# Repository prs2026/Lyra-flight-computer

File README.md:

# Lyra-flight-computer
 repo for the lyra flight computer

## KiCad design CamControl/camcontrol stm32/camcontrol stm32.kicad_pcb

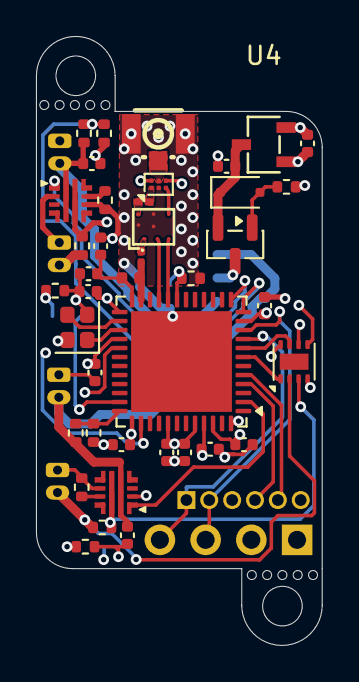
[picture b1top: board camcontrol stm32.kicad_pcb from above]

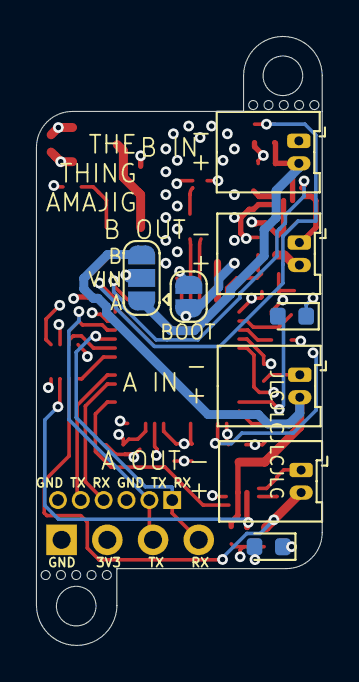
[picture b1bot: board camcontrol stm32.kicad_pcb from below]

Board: 4 copper layers, 15.9 x 33.8 mm, 52 parts (12 on the bottom side), 40 nets.

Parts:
AE1: Antenna_Shield; ANT-SMD_1909763-1
C1, C5, C6, C12: 1u; C_0402_1005Metric
C2: 68p; C_0201_0603Metric
C3: 100p; C_0201_0603Metric
C4, C7: 47n; C_0402_1005Metric
C8, C9, C10, C11, C13, C14, C22: 100n; C_0402_1005Metric
C18: 470n; C_0402_1005Metric
D1, D2: LED; LED_0603_1608Metric
D3: D_Zener; D_SOD-323F
H1, H2: MountingHole; MountingHole_2.2mm_M2_DIN965
J1, J3, J4, J7: Power 1; Molex_PicoBlade_53048-0210_1x02_P1.25mm_Horizontal
J2: Conn_01x04; PinHeader_1x04_P2.54mm_Vertical
J5: Conn_01x06; PinHeader_1x06_P1.27mm_Vertical
J6: Conn_01x02; SolderJumper-2_P1.3mm_Open_RoundedPad1.0x1.5mm
JP1: Jumper; SolderJumper-3_P1.3mm_Open_RoundedPad1.0x1.5mm
L1: 47n; L_0402_1005Metric
Q1: AO3401A; SOT-23
R1, R7: 1k; R_0402_1005Metric
R2, R6: 510; R_0402_1005Metric
R3, R5: 10m; R_0402_1005Metric
R4: 33k; R_0402_1005Metric
R8, R23: 15k; R_0402_1005Metric
R9, R10, R24: 51k; R_0402_1005Metric
U1: BGS12P2L6; Infineon_PG-TSNP-6-10_0.7x1.1mm_0.7x1.1mm_P0.4mm
U2: BALFHB-WL-02D3; CSPG-8_L2.1-W1.8_BALFHB-WL-03D3
U3: STM32WLE4CCUx; QFN-48-1EP_7x7mm_P0.5mm_EP5.6x5.6mm
U4: DS8242; SOT-23-3_L2.9-W1.6-P1.90-LS2.8-BR
U5, U6: TPS25970LRPWR; QFN-10-2x2-hotrod
U7: INA2180; WSON-8-1EP_2x2mm_P0.5mm_EP0.9x1.6mm
Y1: 32MHz; Crystal_SMD_2016-4Pin_2.0x1.6mm

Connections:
+3V3: C6.1, C8.1, C9.1, C10.1, C11.1, C13.1, C14.1, C22.1, D1.2 (A), J2.2, U1.4 (VDD), U3.11 (VDD), U3.25 (VDDPA), U3.28 (VDDRF), U3.37 (VBAT), U3.41 (VDDA), U3.44 (VDD), U3.46 (VDDSMPS), U4.2 (Vout), U7.8 (VS)
+12V: C12.1, J1.2, JP1.1 (A), R23.1, U6.5 (IN)
+12VA: C1.1, J4.2, JP1.3 (B), R8.1, U5.5 (IN)
/BATT SENSE A: R8.2, R9.1, U3.36 (PA13)
/BATT SENSE B: R23.2, R24.1, U3.12 (PA4)
/BOOTSEL: J6.2, R4.2, U3.19 (PH3)
/CAM1 RX: J2.4, J5.1, U3.9 (PA2)
/CAM1 TX: J2.3, J5.2, U3.10 (PA3)
/CAM2 RX: J5.4, U3.4 (PB6)
/CAM2 TX: J5.5, U3.5 (PB7)
/CURRENT SENSE A: U3.7 (PA0), U7.1 (OUT1)
/CURRENT SENSE B: U3.8 (PA1), U7.7 (OUT2)
/LED INDICATION: D2.2 (A), U3.35 (PA12)
/OSC_IN: U3.26 (OSC_IN), Y1.3
/OSC_OUT: U3.27 (OSC_OUT), Y1.1
/PRWA EN: U3.2 (PB4), U5.1 (EN/UVLO)
/PWR A: J7.2, R5.2, U7.2 (IN-1)
/PWR A SENS: R5.1, U5.6 (OUT), U7.3 (IN+1)
/PWR B: J3.2, R3.2, U7.6 (IN-2)
/PWR B SENS: R3.1, U6.6 (OUT), U7.5 (IN+2)
/PWRB EN: U3.13 (PA5), U6.1 (EN/UVLO)
/RF CTRL: U1.6 (CTRL), U3.38 (PC13)
/VFBSMPS: C18.1, U3.29 (VDDRF1V55), U3.45 (VFBSMPS)
/VR_PA: C4.2, C7.2, L1.1, U3.24 (VR_PA)
GND: AE1.2 (Shield), C1.2, C4.1, C5.2, C6.2, C7.1, C8.2, C9.2, C10.2, C11.2, C12.2, C13.2, C14.2, C18.2, C22.2, J1.1, J2.1, J3.1, J4.1, J5.3, J5.6, J6.1, J7.1, R1.2, R2.2, R4.1, R6.2, R7.2, R9.2, R10.2, R24.2, U1.2 (GND), U2.B1 (GND2), U2.B2 (GND3), U2.C2 (GND1), U3.48 (VSSSMPS), U3.49 (VSS), U4.1 (GND), U5.2 (OLVO), U5.8 (GND), U6.2 (OLVO), U6.8 (GND), U7.4 (GND), Y1.2, Y1.4
unnamed: AE1.1 (A), U1.5 (RFIN)
unnamed: D1.1 (K), R1.1
unnamed: D2.1 (K), R7.1
unnamed: D3.2 (A), Q1.1 (G), R10.1
unnamed: C5.1, D3.1 (K), Q1.2 (S), U4.3 (Vin)
unnamed: JP1.2 (C), Q1.3 (D)
unnamed: U1.3 (RF1), U2.C3 (RFI_in)
unnamed: C2.1, U1.1 (RF2)
unnamed: U2.A2 (RFI_N_out), U3.21 (RFI_N)
unnamed: U2.A3 (RFI_P_out), U3.20 (RFI_P)
unnamed: C3.1, U2.A1 (RFO_in)
unnamed: C2.2, U2.C1 (RFO_out)
unnamed: C3.2, L1.2, U3.23 (RFO_HP)
unnamed: R6.1, U5.9 (ILM)
unnamed: R2.1, U6.9 (ILM)

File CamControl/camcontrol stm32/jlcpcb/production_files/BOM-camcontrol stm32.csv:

Comment,Designator,Footprint,LCSC,Quantity
100n,"C10,C11,C13,C14,C22,C8,C9",C_0402_1005Metric,C1525,7
100p,C3,C_0201_0603Metric,C1546,1
10m,"R3,R5",R_0402_1005Metric,C3024467,2
15k,"R23,R8",R_0402_1005Metric,C25756,2
1k,"R1,R7",R_0402_1005Metric,C11702,2
1u,"C1,C12,C5,C6",C_0402_1005Metric,C52923,4
32MHz,Y1,Crystal_SMD_2016-4Pin_2.0x1.6mm,C383840,1
33k,R4,R_0402_1005Metric,C25779,1
470n,C18,C_0402_1005Metric,C47339,1
47n,L1,L_0402_1005Metric,C22334,1
47n,"C4,C7",C_0402_1005Metric,C5142571,2
510,"R2,R6",R_0402_1005Metric,C25123,2
51k,"R10,R24,R9",R_0402_1005Metric,C25794,3
68p,C2,C_0201_0603Metric,C14441,1
AO3401A,Q1,SOT-23,C15127,1
Antenna_Shield,AE1,ANT-SMD_1909763-1,C392444,1
BALFHB-WL-02D3,U2,CSPG-8_L2.1-W1.8_BALFHB-WL-03D3,C5350082,1
BGS12P2L6,U1,Infineon_PG-TSNP-6-10_0.7x1.1mm_0.7x1.1mm_P0.4mm,C3312945,1
DS8242,U4,SOT-23-3_L2.9-W1.6-P1.90-LS2.8-BR,C5884134,1
D_Zener,D3,D_SOD-323F,C7420320,1
INA2180,U7,WSON-8-1EP_2x2mm_P0.5mm_EP0.9x1.6mm,C83224,1
LED,"D1,D2",LED_0603_1608Metric,C89811,2
STM32WLE4CCUx,U3,QFN-48-1EP_7x7mm_P0.5mm_EP5.6x5.6mm,C2888218,1
TPS25970LRPWR,"U5,U6",QFN-10-2x2-hotrod,C3662801,2

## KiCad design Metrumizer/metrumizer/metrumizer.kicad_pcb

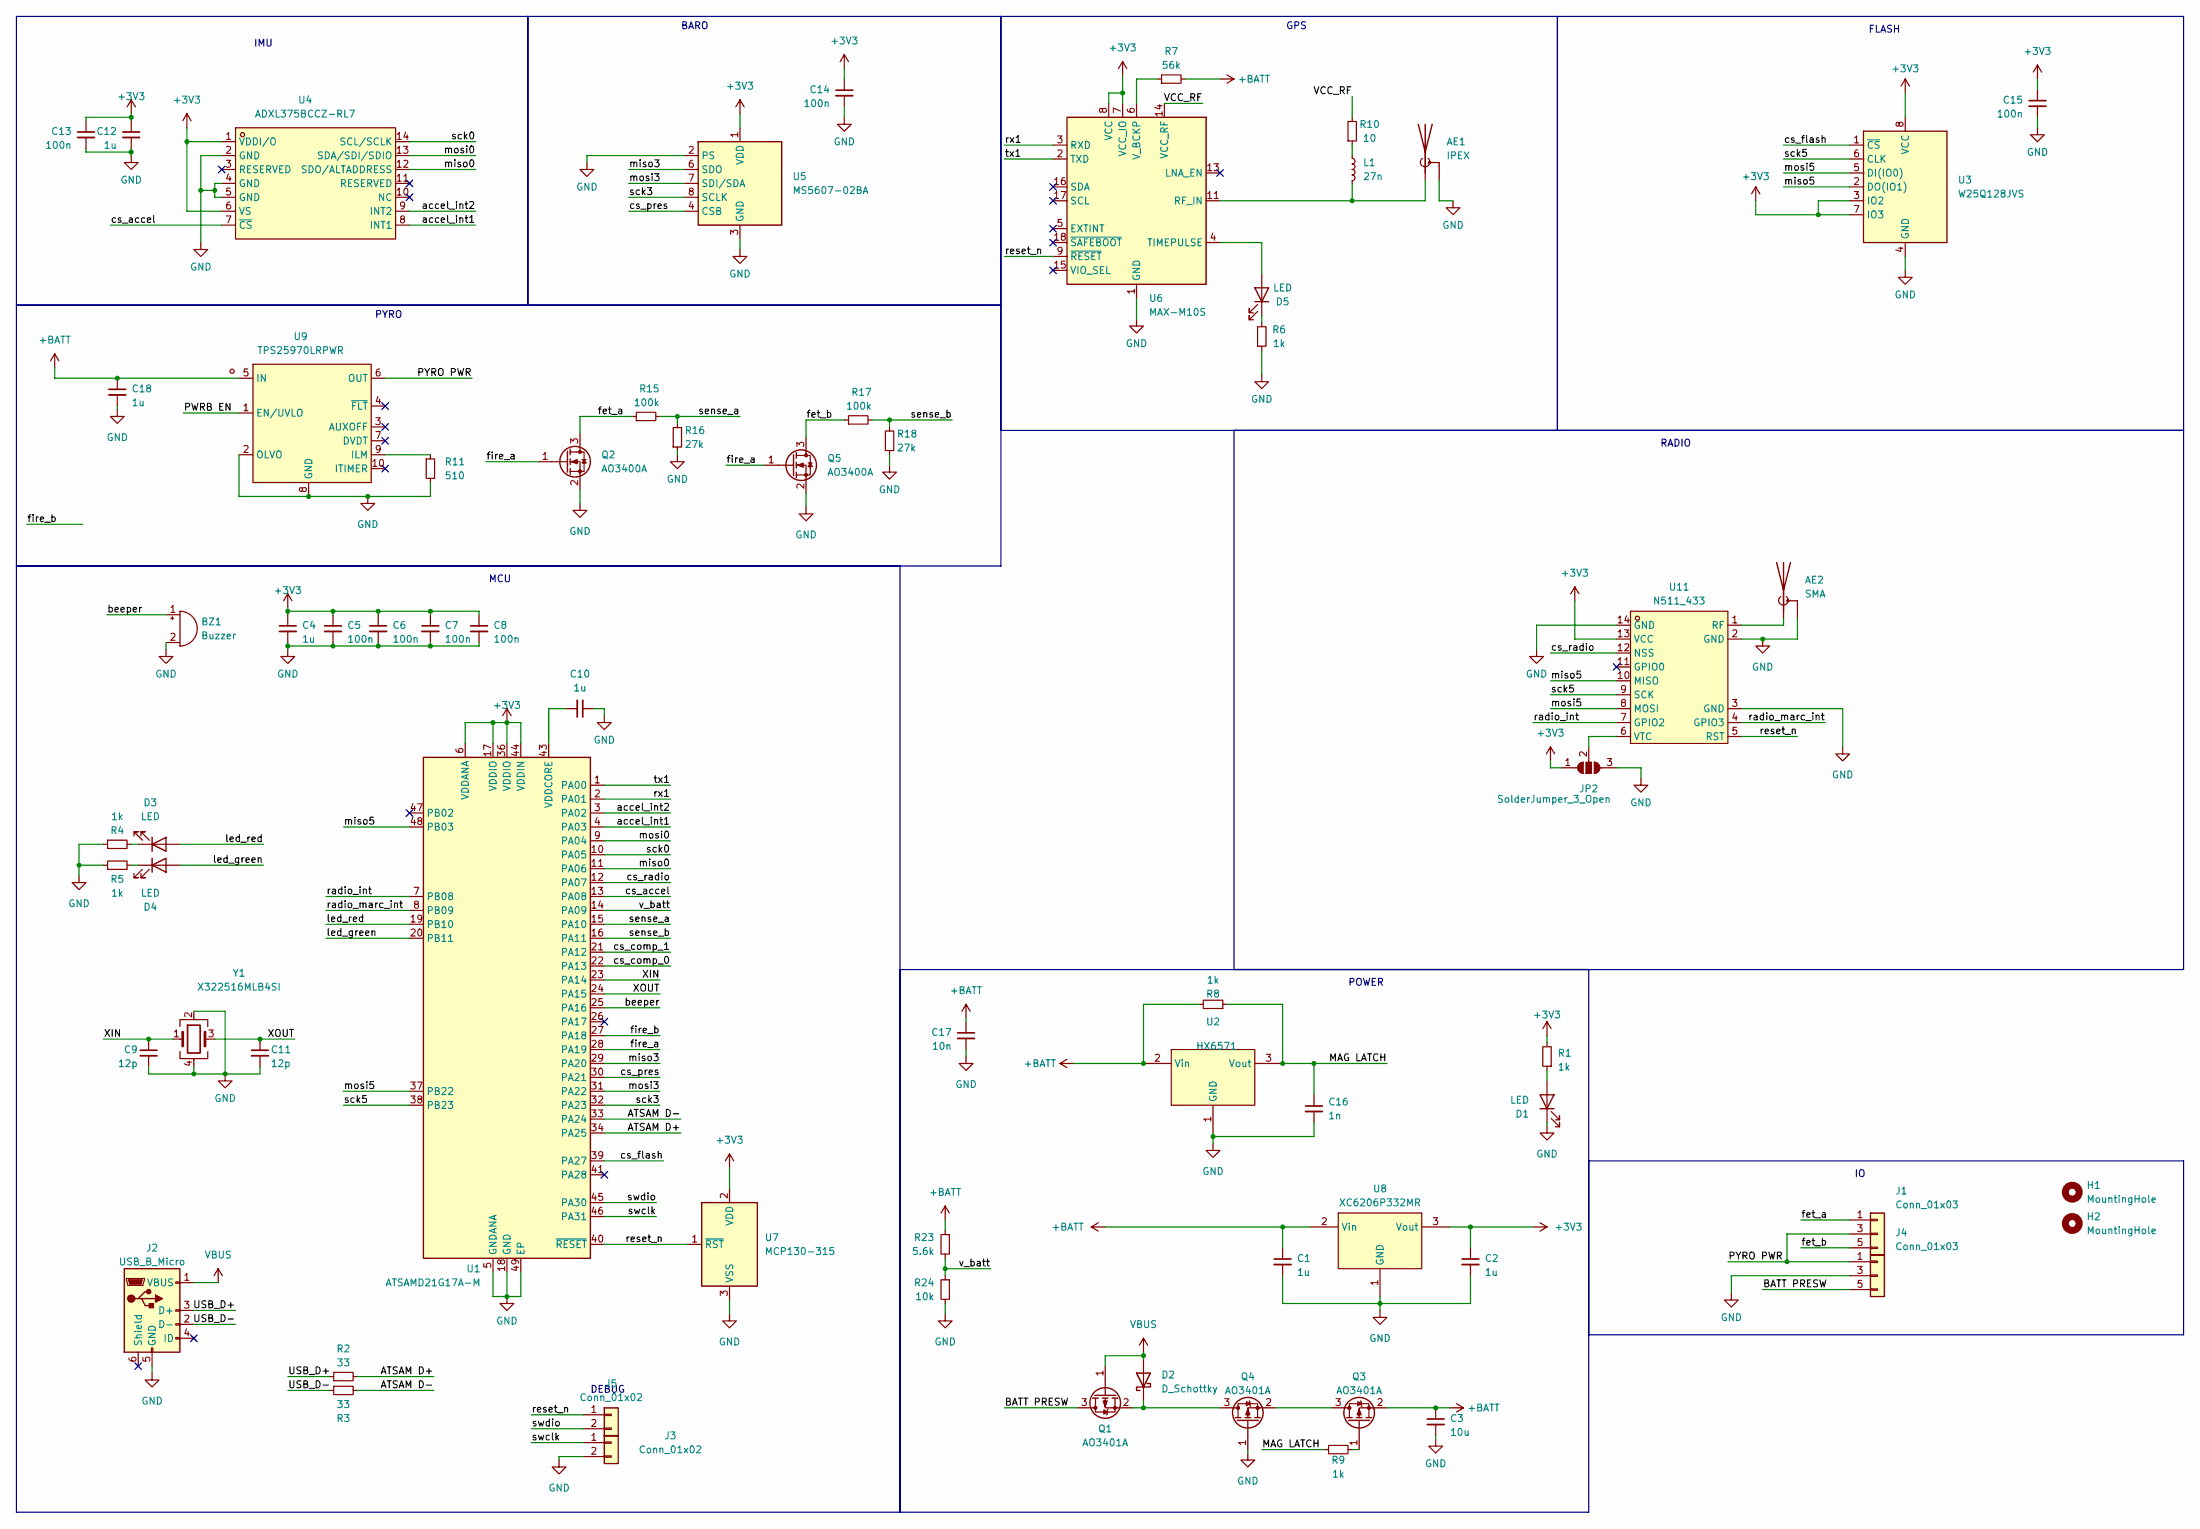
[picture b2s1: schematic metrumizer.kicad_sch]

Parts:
AE1: IPEX; ANT-SMD_1909763-1; LCSC Part C392444
AE2: SMA; CONN-SMD_KH-SMA-KE8-G; LCSC Part C530661
BZ1: Buzzer; PKMCS0909E4000R1; Part # CPE-163
C1, C2, C4, C10, C12, C18: 1u; C_0402_1005Metric; LCSC Part C52923
C3: 10u; C_0603_1608Metric; LCSC Part C96446
C5, C6, C7, C8, C13, C14, C15: 100n; C_0402_1005Metric; LCSC Part C1525
C9, C11: 12p; C_0402_1005Metric; LCSC Part C1547
C16: 1n; C_0402_1005Metric; LCSC Part C1523
C17: 10n; C_0402_1005Metric; LCSC Part C15195
D1, D3, D4, D5: LED; LED_0805_2012Metric
D2: D_Schottky; D_SOD-323F; LCSC Part C191023
H1, H2: MountingHole; MountingHole_3.2mm_M3
J1, J4: Conn_01x03; CONN3_2059-303&slash_998-403_WAG; Part # 2059-323/998-403
J2: USB_B_Micro; MICRO-USB-SMD_U254-051T-4BHJ25-F2S; LCSC Part C381143
J3, J5: Conn_01x02; SolderJumper-2_P1.3mm_Open_Pad1.0x1.5mm
JP2: SolderJumper_3_Open; SolderJumper-3_P1.3mm_Open_RoundedPad1.0x1.5mm
L1: 27n; L_0402_1005Metric; Part # LQG15HS27NJ02D; LCSC Part C18830
Q1, Q3, Q4: AO3401A; SOT-23; LCSC Part C15127
Q2, Q5: AO3400A; SOT-23
R1, R4, R5, R6, R8, R9: 1k; R_0402_1005Metric; LCSC Part C11702
R2, R3: 33; R_0402_1005Metric; LCSC Part C25105
R7: 56k; R_0402_1005Metric; LCSC Part C25796
R10: 10; R_0402_1005Metric; LCSC Part C11702
R11: 510; R_0402_1005Metric; LCSC Part C25123
R15, R17: 100k; R_0402_1005Metric; LCSC Part C11702
R16, R18: 27k; R_0402_1005Metric; LCSC Part C25771
R23: 5.6k; R_0402_1005Metric; LCSC Part C25908
R24: 10k; R_0402_1005Metric; LCSC Part C25744
U1: ATSAMD21G17A-M; QFN-48-1EP_7x7mm_P0.5mm_EP5.15x5.15mm; LCSC Part C614532
U2: HX6571; SOT-23-3_L2.9-W1.6-P1.90-LS2.8-BR; LCSC Part C495738
U3: W25Q128JVS; SOIC-8_5.23x5.23mm_P1.27mm; LCSC Part C97521
U4: ADXL375BCCZ-RL7; LGA-14_L5.0-W3.0-P0.80-BL; LCSC Part C481898
U5: MS5607-02BA; LGA-8_3x5mm_P1.25mm; LCSC Part C97627
U6: MAX-M10S; ublox_MAX
U7: MCP130-315; SOT-23; LCSC Part C625194
U8: XC6206P332MR; SOT-23-3; LCSC Part C5446
U9: TPS25970LRPWR; QFN-10-2x2-hotrod; LCSC Part C3662801
U11: N511_433; N511 433
Y1: X322516MLB4SI; Crystal_SMD_3225-4Pin_3.2x2.5mm; LCSC Part C5444547

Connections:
+3V3: C2.1, C4.1, C5.1, C6.1, C7.1, C8.1, C12.1, C13.1, C14.1, C15.1, JP2.1 (A), R1.2, U1.6 (VDDANA), U1.17 (VDDIO), U1.36 (VDDIO), U1.44 (VDDIN), U3.3 (IO2), U3.7 (IO3), U3.8 (VCC), U4.1 (VDDI/O), U4.6 (VS), U5.1 (VDD), U6.7 (VCC_IO), U6.8 (VCC), U7.2 (VDD), U8.3 (Vout), U11.13 (VCC)
+BATT: C1.1, C3.1, C17.1, C18.1, Q3.2 (S), R7.2, R8.2, R23.1, U2.2 (Vin), U8.2 (Vin), U9.5 (IN)
/ATSAM D+: R2.2, U1.34 (PA25)
/ATSAM D-: R3.2, U1.33 (PA24)
/BATT PRESW: J4.5 (Pin_3), J4.6 (Pin_3), Q1.3 (D)
/MAG LATCH: C16.1, R8.1, R9.1, U2.3 (Vout)
/PWRB EN: U9.1 (EN/UVLO)
/PYRO PWR: J1.3 (Pin_2), J1.4 (Pin_2), J4.1, J4.2 (Pin_1), U9.6 (OUT)
/USB_D+: J2.3 (D+), R2.1
/USB_D-: J2.2 (D-), R3.1
/VCC_RF: R10.2, U6.14 (VCC_RF)
/XIN: C9.1, U1.23 (PA14), Y1.1
/XOUT: C11.1, U1.24 (PA15), Y1.3
/accel_int1: U1.4 (PA03), U4.8 (INT1)
/accel_int2: U1.3 (PA02), U4.9 (INT2)
/beeper: BZ1.1 (+), U1.25 (PA16)
/cs_accel: U1.13 (PA08), U4.7 (~CS)
/cs_comp_0: U1.22 (PA13)
/cs_comp_1: U1.21 (PA12)
/cs_flash: U1.39 (PA27), U3.1 (~CS)
/cs_pres: U1.30 (PA21), U5.4 (CSB), U5.5 (CSB)
/cs_radio: U1.12 (PA07), U11.12 (NSS)
/fet_a: J1.1, J1.2 (Pin_1), Q2.3 (D), R15.1
/fet_b: J1.5 (Pin_3), J1.6 (Pin_3), Q5.3 (D), R17.1
/fire_a: Q2.1 (G), Q5.1 (G), U1.28 (PA19)
/fire_b: U1.27 (PA18)
/led_green: D4.2 (A), U1.20 (PB11)
/led_red: D3.2 (A), U1.19 (PB10)
/miso0: U1.11 (PA06), U4.12 (SDO/ALTADDRESS)
/miso3: U1.29 (PA20), U5.6 (SDO)
/miso5: U1.48 (PB03), U3.2 (DO(IO1)), U11.10 (MISO)
/mosi0: U1.9 (PA04), U4.13 (SDA/SDI/SDIO)
/mosi3: U1.31 (PA22), U5.7 (SDI/SDA)
/mosi5: U1.37 (PB22), U3.5 (DI(IO0)), U11.8 (MOSI)
/radio_int: U1.7 (PB08), U11.7 (GPIO2)
/radio_marc_int: U1.8 (PB09), U11.4 (GPIO3)
/reset_n: J5.1, U1.40 (~RESET), U6.9 (~RESET), U7.1 (~RST), U11.5 (RST)
/rx1: U1.2 (PA01), U6.3 (RXD)
/sck0: U1.10 (PA05), U4.14 (SCL/SCLK)
/sck3: U1.32 (PA23), U5.8 (SCLK)
/sck5: U1.38 (PB23), U3.6 (CLK), U11.9 (SCK)
/sense_a: R15.2, R16.2, U1.15 (PA10)
/sense_b: R17.2, R18.2, U1.16 (PA11)
/swclk: J3.1, U1.46 (PA31)
/swdio: J5.2, U1.45 (PA30)
/tx1: U1.1 (PA00), U6.2 (TXD)
/v_batt: R23.2, R24.1, U1.14 (PA09)
GND: AE1.2 (Shield), AE2.2 (Shield), BZ1.2 (-), C1.2, C2.2, C3.2, C4.2, C5.2, C6.2, C7.2, C8.2, C9.2, C10.1, C11.2, C12.2, C13.2, C14.2, C15.2, C16.2, C17.2, C18.2, D1.1 (K), J2.5 (GND), J3.2, J4.3 (Pin_2), J4.4 (Pin_2), JP2.3 (B), Q2.2 (S), Q4.1 (G), Q5.2 (S), R4.1, R5.1, R6.1, R11.2, R16.1, R18.1, R24.2, U1.5 (GNDANA), U1.18 (GND), U1.35 (GND), U1.42 (GND), U1.49 (EP), U2.1 (GND), U3.4 (GND), U4.2 (GND), U4.4 (GND), U4.5 (GND), U5.2 (PS), U5.3 (GND), U6.1 (GND), U6.10 (GND), U6.12 (GND), U7.3 (VSS), U8.1 (GND), U9.2 (OLVO), U9.8 (GND), U11.2 (GND), U11.3 (GND), U11.14 (GND), Y1.2, Y1.4
unnamed: AE1.1 (A), L1.2, U6.11 (RF_IN)
unnamed: AE2.1 (A), U11.1 (RF)
unnamed: D1.2 (A), R1.1
unnamed: D2.1 (K), Q1.2 (S), Q4.3 (D)
unnamed: D3.1 (K), R4.2
unnamed: D4.1 (K), R5.2
unnamed: D5.2 (A), U6.4 (TIMEPULSE)
unnamed: D5.1 (K), R6.2
unnamed: JP2.2 (C), U11.6 (VTC)
unnamed: L1.1, R10.1
unnamed: Q3.3 (D), Q4.2 (S)
unnamed: Q3.1 (G), R9.2
unnamed: C10.2, U1.43 (VDDCORE)
unnamed: R7.1, U6.6 (V_BCKP)
unnamed: R11.1, U9.9 (ILM)
VBUS: D2.2 (A), J2.1 (VBUS), Q1.1 (G)

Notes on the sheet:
IMU
PYRO
DEBUG
GPS
MCU
BARO
RADIO
POWER
FLASH

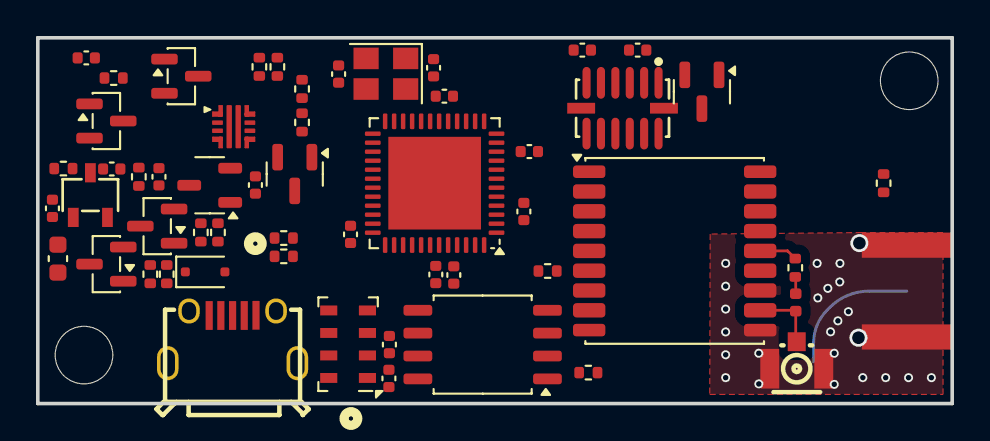
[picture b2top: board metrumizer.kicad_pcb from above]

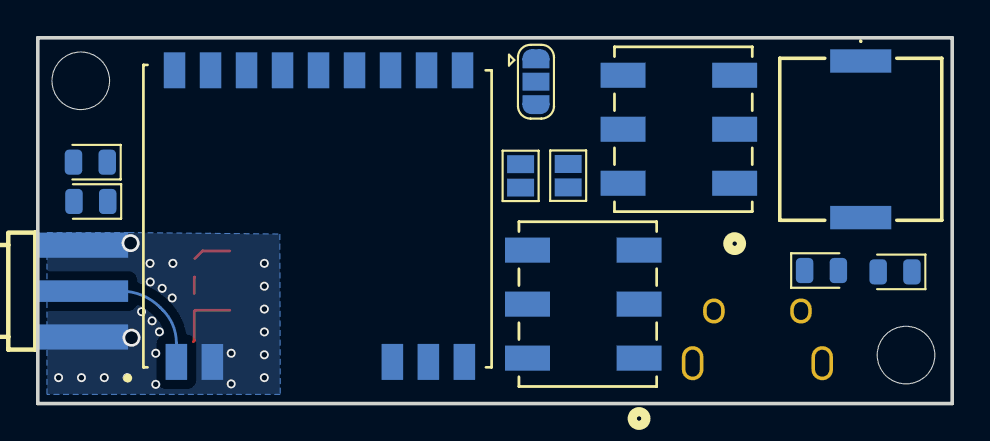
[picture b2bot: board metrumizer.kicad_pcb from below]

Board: 4 copper layers, 50.8 x 20.3 mm, 68 parts (13 on the bottom side), 60 nets.

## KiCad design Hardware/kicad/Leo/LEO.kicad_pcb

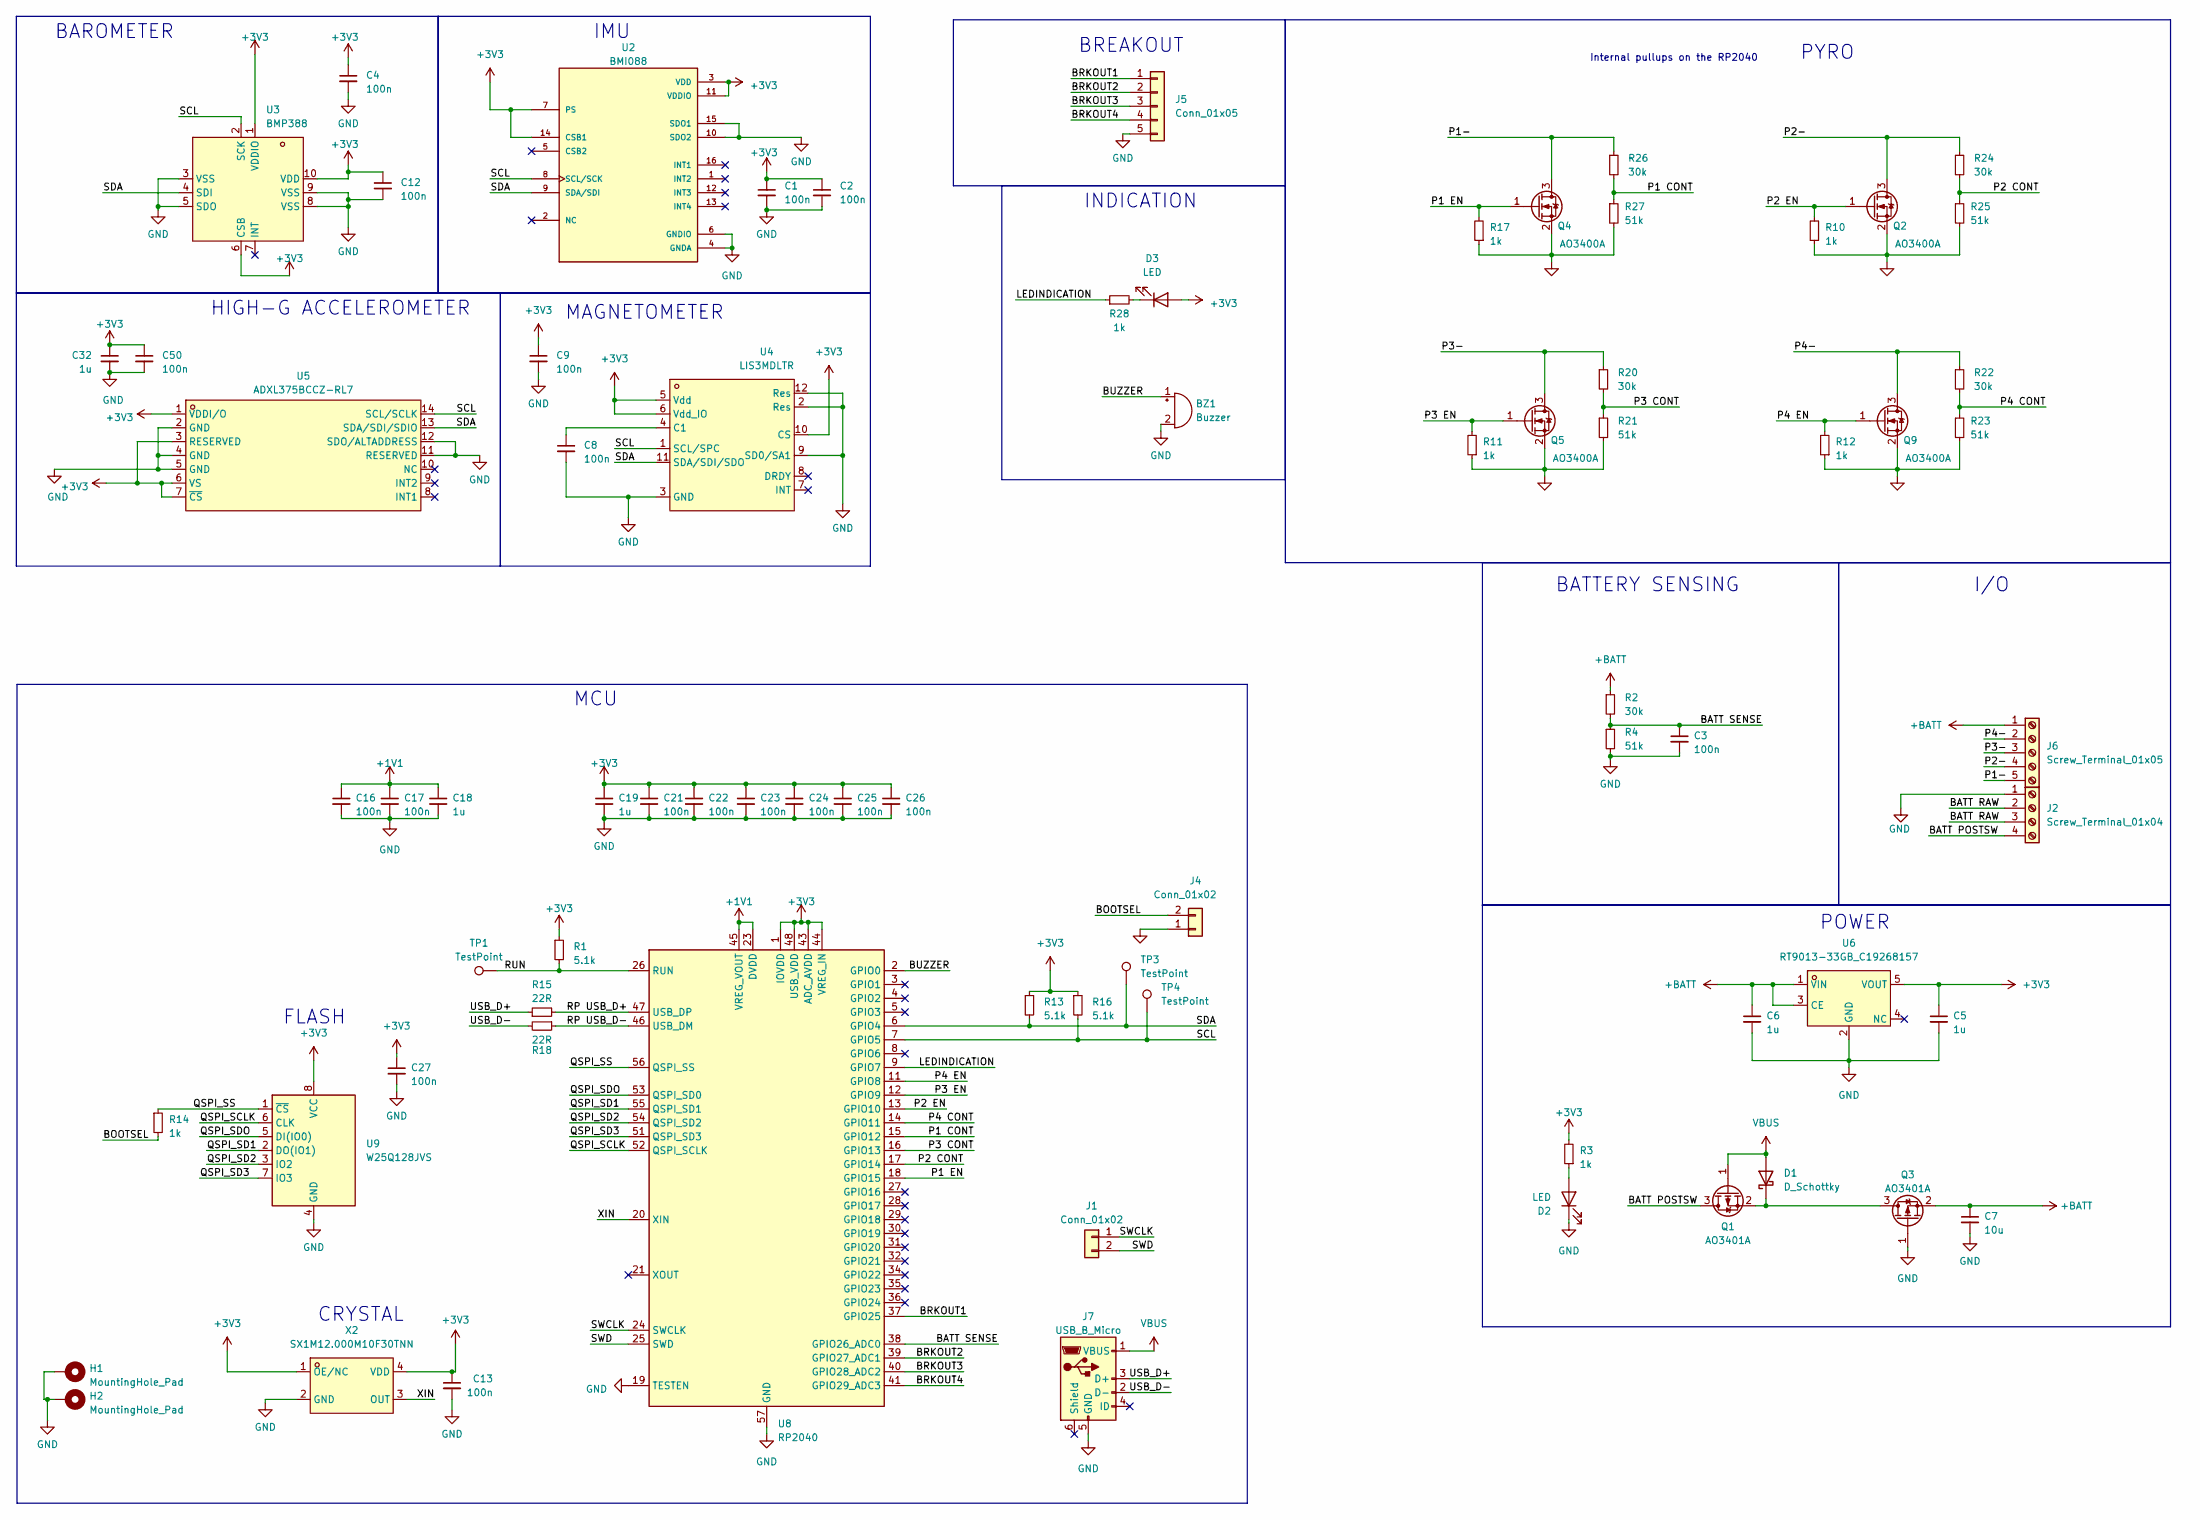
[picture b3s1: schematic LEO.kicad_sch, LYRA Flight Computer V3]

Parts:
BZ1: Buzzer; PKMCS0909E4000R1; Part # CPE-163
C1, C2, C3, C4, C8, C9, C12, C13, C16, C17, C21, C22, C23, C24, C25, C26, C27, C50: 100n; C_0402_1005Metric; LCSC Part C1525
C5, C6, C18, C19, C32: 1u; C_0402_1005Metric; LCSC Part C52923
C7: 10u; C_0603_1608Metric; LCSC Part C96446
D1: D_Schottky; D_SOD-323F; LCSC Part C191023
D2, D3: LED; LED_0805_2012Metric
H1, H2: MountingHole_Pad; MountingHole_2.2mm_M2_DIN965_Pad
J1: Conn_01x02; SolderJumper-2_P1.3mm_Open_Pad1.0x1.5mm
J2: Screw_Terminal_01x04; TerminalBlock_Phoenix_MPT-0,5-4-2.54_1x04_P2.54mm_Horizontal
J4: Conn_01x02; SolderJumper-2_P1.3mm_Open_RoundedPad1.0x1.5mm
J5: Conn_01x05; Pad_01x_05
J6: Screw_Terminal_01x05; TerminalBlock_Phoenix_MPT-0,5-5-2.54_1x05_P2.54mm_Horizontal
J7: USB_B_Micro; MICRO-USB-SMD_U254-051T-4BHJ25-F2S; LCSC Part C381143
Q1, Q3: AO3401A; SOT-23; LCSC Part C15127
Q2, Q4, Q5, Q9: AO3400A; SOT-23; LCSC Part C20917
R1, R13, R16: 5.1k; R_0402_1005Metric; LCSC Part C25905
R2, R20, R22, R24, R26: 30k; R_0402_1005Metric; LCSC Part C25105
R3, R10, R11, R12, R14, R17, R28: 1k; R_0402_1005Metric; LCSC Part C11702
R4, R21, R23, R25, R27: 51k; R_0402_1005Metric
R15, R18: 22R; R_0402_1005Metric; LCSC Part C25092
TP1, TP3, TP4: TestPoint; TestPoint_Pad_1.0x1.0mm
U2: BMI088; LGA-16_L4.5-W3.0-P0.50-BL; LCSC Part C194919
U3: BMP388; SENSORM-SMD_BMP388; LCSC Part C779278
U4: LIS3MDLTR; LGA-12_L2.0-W2.0-P0.50-BL; LCSC Part C478483
U5: ADXL375BCCZ-RL7; LGA-14_L5.0-W3.0-P0.80-BL; LCSC Part C481898
U6: RT9013-33GB_C19268157; SOT-23-5_L2.9-W1.6-P0.95-LS2.8-BR; LCSC Part C19268157
U8: RP2040; QFN-56-1EP_7x7mm_P0.4mm_EP3.2x3.2mm; LCSC Part C2040
U9: W25Q128JVS; SOIC-8_5.23x5.23mm_P1.27mm; LCSC Part C97521
X2: SX1M12.000M10F30TNN; OSC-SMD_4P-L2.0-W1.6-BL; LCSC Part C2901608

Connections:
+1V1: C16.1, C17.1, C18.1, U8.23 (DVDD), U8.45 (VREG_VOUT), U8.50 (DVDD)
+3V3: C1.1, C2.1, C4.1, C5.1, C9.1, C12.1, C13.1, C19.1, C21.1, C22.1, C23.1, C24.1, C25.1, C26.1, C27.1, C32.1, C50.1, D3.2 (A), R1.1, R3.2, R13.1, R16.1, U2.3 (VDD), U2.7 (PS), U2.11 (VDDIO), U2.14 (CSB1), U3.1 (VDDIO), U3.6 (CSB), U3.10 (VDD), U4.5 (Vdd), U4.6 (Vdd_IO), U4.10 (CS), U5.1 (VDDI/O), U5.3 (RESERVED), U5.6 (VS), U5.7 (~CS), U6.5 (VOUT), U8.1 (IOVDD), U8.10 (IOVDD), U8.22 (IOVDD), U8.33 (IOVDD), U8.42 (IOVDD), U8.43 (ADC_AVDD), U8.44 (VREG_IN), U8.48 (USB_VDD), U8.49 (IOVDD), U9.8 (VCC), X2.1 (OE/NC), X2.4 (VDD)
+BATT: C6.1, C7.1, J6.1, Q3.2 (S), R2.1, U6.1 (VIN), U6.3 (CE)
/BATT POSTSW: J2.4, Q1.3 (D)
/BATT RAW: J2.2, J2.3
/BATT SENSE: C3.1, R2.2, R4.1, U8.38 (GPIO26_ADC0)
/BOOTSEL: J4.2, R14.2
/BRKOUT1: J5.1, U8.37 (GPIO25)
/BRKOUT2: J5.2, U8.39 (GPIO27_ADC1)
/BRKOUT3: J5.3, U8.40 (GPIO28_ADC2)
/BRKOUT4: J5.4, U8.41 (GPIO29_ADC3)
/BUZZER: BZ1.1 (+), U8.2 (GPIO0)
/LEDINDICATION: R28.1, U8.9 (GPIO7)
/P1 CONT: R26.2, R27.1, U8.15 (GPIO12)
/P1 EN: Q4.1 (G), R17.2, U8.18 (GPIO15)
/P1-: J6.5, Q4.3 (D), R26.1
/P2 CONT: R24.2, R25.1, U8.17 (GPIO14)
/P2 EN: Q2.1 (G), R10.2, U8.13 (GPIO10)
/P2-: J6.4, Q2.3 (D), R24.1
/P3 CONT: R20.2, R21.1, U8.16 (GPIO13)
/P3 EN: Q5.1 (G), R11.2, U8.12 (GPIO9)
/P3-: J6.3, Q5.3 (D), R20.1
/P4 CONT: R22.2, R23.1, U8.14 (GPIO11)
/P4 EN: Q9.1 (G), R12.2, U8.11 (GPIO8)
/P4-: J6.2, Q9.3 (D), R22.1
/QSPI_SCLK: U8.52 (QSPI_SCLK), U9.6 (CLK)
/QSPI_SD1: U8.55 (QSPI_SD1), U9.2 (DO(IO1))
/QSPI_SD2: U8.54 (QSPI_SD2), U9.3 (IO2)
/QSPI_SD3: U8.51 (QSPI_SD3), U9.7 (IO3)
/QSPI_SDO: U8.53 (QSPI_SD0), U9.5 (DI(IO0))
/QSPI_SS: R14.1, U8.56 (QSPI_SS), U9.1 (~CS)
/RP USB_D+: R15.2, U8.47 (USB_DP)
/RP USB_D-: R18.1, U8.46 (USB_DM)
/RUN: R1.2, TP1.1, U8.26 (RUN)
/SCL: R16.2, TP4.1, U2.8 (SCL/SCK), U3.2 (SCK), U4.1 (SCL/SPC), U5.14 (SCL/SCLK), U8.7 (GPIO5)
/SDA: R13.2, TP3.1, U2.9 (SDA/SDI), U3.4 (SDI), U4.11 (SDA/SDI/SDO), U5.13 (SDA/SDI/SDIO), U8.6 (GPIO4)
/SWCLK: J1.1, U8.24 (SWCLK)
/SWD: J1.2, U8.25 (SWD)
/USB_D+: J7.3 (D+), R15.1
/USB_D-: J7.2 (D-), R18.2
/XIN: U8.20 (XIN), X2.3 (OUT)
GND: BZ1.2 (-), C1.2, C2.2, C3.2, C4.2, C5.2, C6.2, C7.2, C8.2, C9.2, C12.2, C13.2, C16.2, C17.2, C18.2, C19.2, C21.2, C22.2, C23.2, C24.2, C25.2, C26.2, C27.2, C32.2, C50.2, D2.1 (K), H1.1, H2.1, J2.1, J4.1, J5.5, J7.5 (GND), Q2.2 (S), Q3.1 (G), Q4.2 (S), Q5.2 (S), Q9.2 (S), R4.2, R10.1, R11.1, R12.1, R17.1, R21.2, R23.2, R25.2, R27.2, U2.4 (GNDA), U2.6 (GNDIO), U2.10 (SDO2), U2.15 (SDO1), U3.3 (VSS), U3.5 (SDO), U3.8 (VSS), U3.9 (VSS), U4.2 (Res), U4.3 (GND), U4.9 (SD0/SA1), U4.12 (Res), U5.2 (GND), U5.4 (GND), U5.5 (GND), U5.11 (RESERVED), U5.12 (SDO/ALTADDRESS), U6.2 (GND), U8.19 (TESTEN), U8.57 (GND), U9.4 (GND), X2.2 (GND)
unnamed: D1.1 (K), Q1.2 (S), Q3.3 (D)
unnamed: D2.2 (A), R3.1
unnamed: D3.1 (K), R28.2
unnamed: C8.1, U4.4 (C1)
VBUS: D1.2 (A), J7.1 (VBUS), Q1.1 (G)

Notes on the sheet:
HIGH-G ACCELEROMETER
I/O
CRYSTAL
FLASH
IMU
POWER
MAGNETOMETER
BATTERY SENSING
Internal pullups on the RP2040
INDICATION
MCU
PYRO
BAROMETER
BREAKOUT

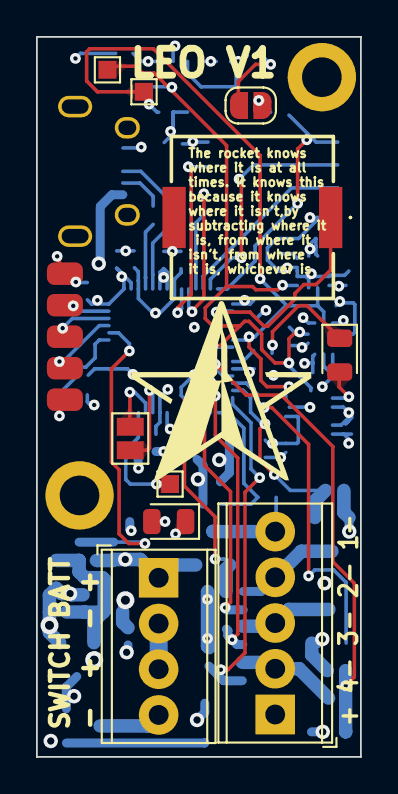
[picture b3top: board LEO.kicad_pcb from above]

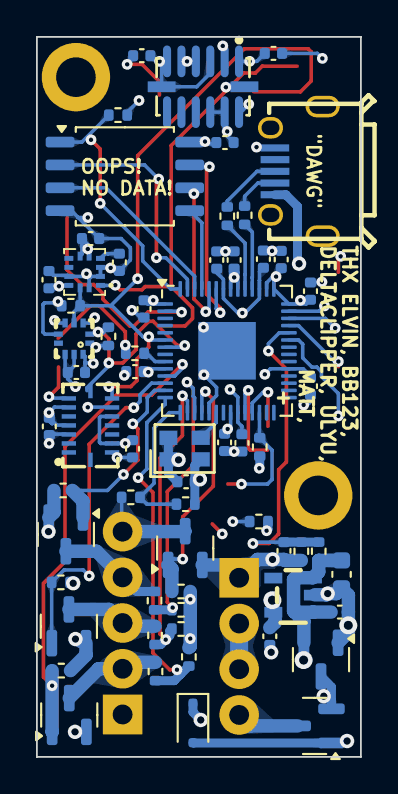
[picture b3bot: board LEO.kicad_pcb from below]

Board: 4 copper layers, 18.0 x 40.0 mm, 75 parts (62 on the bottom side), 47 nets.

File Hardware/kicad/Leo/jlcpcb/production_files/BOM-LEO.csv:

Comment,Designator,Footprint,LCSC
1k,"R10,R11,R12,R14,R17,R28,R3",R_0402_1005Metric,C11702
AO3401A,"Q1,Q3",SOT-23,C15127
100n,"C1,C12,C13,C16,C17,C2,C21,C22,C23,C24,C25,C26,C27,C3,C4,C50,C8,C9",C_0402_1005Metric,C1525
D_Schottky,D1,D_SOD-323F,C191023
RT9013-33GB_C19268157,U6,SOT-23-5_L2.9-W1.6-P0.95-LS2.8-BR,C19268157
BMI088,U2,LGA-16_L4.5-W3.0-P0.50-BL,C194919
RP2040,U8,QFN-56-1EP_7x7mm_P0.4mm_EP3.2x3.2mm,C2040
AO3400A,"Q2,Q4,Q5,Q9",SOT-23,C20917
22R,"R15,R18",R_0402_1005Metric,C25092
30k,"R2,R20,R22,R24,R26",R_0402_1005Metric,C25105
51k,"R21,R23,R25,R27,R4",R_0402_1005Metric,C25794
5.1k,"R1,R13,R16",R_0402_1005Metric,C25905
SX1M12.000M10F30TNN,X2,OSC-SMD_4P-L2.0-W1.6-BL,C2901608
USB_B_Micro,J7,MICRO-USB-SMD_U254-051T-4BHJ25-F2S,C381143
LIS3MDLTR,U4,LGA-12_L2.0-W2.0-P0.50-BL,C478483
ADXL375BCCZ-RL7,U5,LGA-14_L5.0-W3.0-P0.80-BL,C481898
1u,"C18,C19,C32,C5,C6",C_0402_1005Metric,C52923
BMP388,U3,SENSORM-SMD_BMP388,C779278
10u,C7,C_0603_1608Metric,C96446
W25Q128JVS,U9,SOIC-8_5.23x5.23mm_P1.27mm,C97521

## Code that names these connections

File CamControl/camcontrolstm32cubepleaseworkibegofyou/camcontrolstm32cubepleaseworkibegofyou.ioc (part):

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Mcu.Name=STM32WLE5CCUx
Mcu.Package=UFQFPN48
Mcu.UserName=STM32WLE5CCUx
PA12.Signal=GPIO_Output
PA13.GPIOParameters=GPIO_Label
PA13.GPIO_Label=BATT SENSE A
PA13.Mode=IN9
PA13.Signal=ADC_IN9
PA2.Mode=Asynchronous
PA2.Signal=USART2_TX
PA3.Mode=Asynchronous
PA3.Signal=USART2_RX
PA5.GPIOParameters=GPIO_Label
PA5.GPIO_Label=PWR B EN
PA5.Signal=GPIO_Output
PB4.GPIOParameters=GPIO_Label
PB4.GPIO_Label=PRW A EN
PB4.Signal=GPIO_Output
PB6.Signal=USART1_TX
PB7.Signal=USART1_RX
RCC.HSE_VALUE=32000000
board=custom

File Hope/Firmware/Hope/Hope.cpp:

#include <stdio.h>
#include "pico/stdlib.h"
#include "hardware/spi.h"
#include "hardware/clocks.h"
#include "hardware/uart.h"

// SPI Defines
// We are going to use SPI 0, and allocate it to the following GPIO pins
// Pins can be changed, see the GPIO function select table in the datasheet for information on GPIO assignments
#define SPI_PORT spi1
#define PIN_MISO 28
#define PIN_CS   25
#define PIN_SCK  26
#define PIN_MOSI 27

//Radio pins
#define PIN_DIO1 9
#define PIN_DIO2 1
#define PIN_DIO3 0
#define PIN_BUSY 10 // High when busy
#define PIN_TXCOEN 11 // Active high
#define PIN_RST 17 // active low


#define PIN_LED 8


// UART defines
// By default the stdout UART is `uart0`, so we will use the second one
#define UART_ID uart0
#define BAUD_RATE 9600

// Use pins 4 and 5 for UART1
// Pins can be changed, see the GPIO function select table in the datasheet for information on GPIO assignments
#define UART_TX_PIN 12
#define UART_RX_PIN 13

//pulses the NRESET pin low for 10ms
//returns 0 
int resetsx1280(){
    gpio_put(PIN_RST,0);
    sleep_ms(100);
    gpio_put(PIN_RST,1);
    sleep_ms(100);
    printf("resetting sx1280\n");
    return 0;
}

int main()
{
    //Init standard io
    stdio_init_all();

    //wait so init messages can actually be seen on serial
    sleep_ms(5000);

    gpio_set_function(PIN_MISO, GPIO_FUNC_SPI);
    gpio_set_function(PIN_SCK,  GPIO_FUNC_SPI);
    gpio_set_function(PIN_MOSI, GPIO_FUNC_SPI);
    // SPI initialisation. This will use SPI at 12.5kHz.
    spi_init(SPI_PORT, 12500);
    
    
    //gpio inits
    gpio_init(PIN_CS);
    gpio_init(PIN_BUSY);
    gpio_init(PIN_DIO1);
    gpio_init(PIN_DIO2);
    gpio_init(PIN_DIO3);
    gpio_init(PIN_RST);
    gpio_init(PIN_LED);
    //Define pin directions
    gpio_set_dir(PIN_CS, GPIO_OUT);
    gpio_set_dir(PIN_BUSY, GPIO_IN);
    gpio_set_dir(PIN_DIO1, GPIO_IN);
    gpio_set_dir(PIN_DIO2, GPIO_IN);
    gpio_set_dir(PIN_DIO3, GPIO_IN);
    gpio_set_dir(PIN_RST, GPIO_OUT);


    gpio_set_dir(PIN_LED, GPIO_OUT);
    
    // Chip select is active-low, so we'll initialise it to a driven-low state because theres nothing else there
    gpio_put(PIN_CS, 0);
    // TXCOEN is active high, so set high on startup
    gpio_put(PIN_CS, 1);
    // RST is active high, so set low on startup to set high later
    gpio_put(PIN_RST, 0);
    // Turn off LED until setup complete
    gpio_put(PIN_LED, 0);

    // For more examples of SPI use see https://github.com/raspberrypi/pico-examples/tree/master/spi

    // reset the sx1280
    resetsx1280();

    while (gpio_get(PIN_BUSY))
    {
        printf("SX1280 BUSY\n");
        sleep_ms(200);
    }
    uint16_t address = 0x153;
    uint8_t addr_h = address >> 8;
    uint8_t addr_l = address & 0x00FF;

    uint8_t txdata[6] = {0x19,addr_h,addr_l,0xFF,0xFF,0xFF};
    uint8_t rxdata1[4] = {};
    gpio_put(PIN_CS,0);
    spi_write_blocking(spi1,txdata,4);
    spi_read_blocking(spi1,0xFF,rxdata1,4);
    gpio_put(PIN_CS,1);

    printf("recived data: %x %x %x %x\n",rxdata1[0],rxdata1[1],rxdata1[2],rxdata1[3]);
    printf("sent data: %x %x %x %x\n",txdata[0],txdata[1],txdata[2],txdata[3]);
    bool ledstatus = 0;
    while (true) {
        printf("Hello, world!\n");
        if (gpio_get(PIN_BUSY))
        {
            printf("SX1280 BUSY\n");
        }
        sleep_ms(1000);
        gpio_put(PIN_LED, ledstatus);
        ledstatus = !ledstatus;
    }
}



    // // Set up our UART
    // uart_init(UART_ID, BAUD_RATE);
    // // Set the TX and RX pins by using the function select on the GPIO
    // // Set datasheet for more information on function select
    // gpio_set_function(UART_TX_PIN, GPIO_FUNC_UART);
    // gpio_set_function(UART_RX_PIN, GPIO_FUNC_UART);
    

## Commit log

2023-11-15 init
2023-11-15 reorganise
2023-11-16 lyrav3 init
2023-11-16 lyrav3 init fo real
2023-11-16 lyra v3 work
    got most of the sensors and other stuff picked out
2023-11-17 lyrav3 work and more orientation work
2023-11-18 accelworld mostly workign!
2023-11-19 lyra v3 work
2023-11-19 more lyra v3 work and stuff
2023-11-21 lyrav3 and kf work
    added 2nd mcu for lyra and got z accel working for kf
2023-11-22 more lyrav3 work
2023-11-24 more lyrav3 work and improved logging schema
2023-11-24 cadded it, it fits!
2023-11-27 lyra
2023-11-27 bunch of stuff, new rouiting
2023-11-28 stuffs
2023-11-28 got the radio responding to uart
2023-11-30 more lyrav3 work as well as more work on new text file and DMA
2023-12-01 radio still not working
2023-12-01 radio communicating again
    still no actual data though, more work needded
2023-12-04 more lyrv v3 work
2023-12-04 more lyra v3 work
    got rid of the second MCU, just going to use I/O expanders and an ADC
2023-12-04 sync hole footprint
2023-12-04 aghjkl
2023-12-05 upatas
2023-12-06 able to read and write regs of radio, not communicating yet
2023-12-08 simplified lyrav3
2023-12-08 lyrav3update
2023-12-09 lyrav3 work
2023-12-09 upadeta
2023-12-10 more everything to back of board, find JLC components for everything
2023-12-11 routing init
2023-12-11 silkscreen work and add parser to display rotation data
2023-12-11 more work on the data displayer
2023-12-13 move aruond
2023-12-13 routing twioce
2023-12-13 rout lyrav3 fully
2023-12-13 routing and updating lcsc part nums
2023-12-14 tring to get the radio to work
2023-12-14 bom and stuff
2023-12-14 radio working with library
2023-12-14 radio not really working
2023-12-15 radio work
2023-12-15 radio not reeally workign
2023-12-16 pre trip, radios pretty much working
2023-12-16 edits
2023-12-16 real pretrip
2023-12-16 setting up telemetry
2023-12-17 radios communicating but data still borked
2023-12-18 change baro to dps310
2023-12-19 fixed more stuff with the library, got telemetry down
2023-12-19 autosave before slep
2023-12-20 buasuig
2023-12-20 radios working again
2023-12-20 radios somewhat working
2023-12-23 radios like kinda sorta working
    still no two way after launch detect mode set, but goodish before then
2023-12-23 found new brownout cap
2023-12-24 new routing and other stuff
    add brownout cap
2023-12-25 post order commit
2023-12-27 qwerty
2023-12-28 restructure and divide into cpp vs h files
2023-12-28 got vscode happy
2023-12-31 lero stuff and init
2023-12-31 stufss
2024-01-01 autosave
2024-01-03 pre unstructureing
2024-01-04 got it complining
2024-01-04 booting and stuff
2024-01-04 built cad
2024-01-05 adxl working and datalogging work
2024-01-06 lero schematic
2024-01-06 schemtic before soildering
2024-01-06 schematic
2024-01-06 add lib
2024-01-07 still not working
2024-01-08 lcd kinda workign with nano
2024-01-08 autosaves
2024-01-08 adias
2024-01-09 adxl workin
2024-01-11 lcd working on main board
2024-01-17 lots of stuff
    radios working, filter sort of working, reciver talking to itself and talking, lcd working
2024-01-17 stuff like kinda talkin
2024-01-18 kalman sort of working
2024-01-19 state kinda working
2024-01-22 post flight commit
2024-01-22 log creats
2024-01-23 added pyro func
2024-01-24 pyros kinda?
2024-01-24 pyros firing
2024-01-24 python getter script
2024-01-25 logging and logging script work
2024-01-25 add gps module init
2024-01-26 beeping more consitant but blocking
2024-01-28 pre flight commit
2024-01-28 THINGS
2024-02-04 post flght commit
2024-02-04 post flight with changes
2024-02-11 made it buffer + log at launch
2024-02-11 kinda doing better logging, not really working yet
2024-02-14 logging totally working
2024-02-14 got it reciving the logs baybee
2024-02-14 added comments
2024-02-19 init v3r1
2024-02-20 fixed klauch deyect
2024-02-20 got logs down
2024-02-24 aesrgd
2024-02-27 gps thingings
2024-02-27 more radio stuffs
2024-02-28 stuffs
    more telemetry work, selected oscilator
2024-02-29 gps init, moar librarys
2024-03-03 magswitch lol
2024-03-04 magswitch work
2024-03-05 gps and rf
2024-03-06 work
2024-03-07 stufffff
2024-03-08 change back to sx1262
2024-03-09 w45dytfv
2024-03-20 asdfghj
2024-03-20 redoing stuff
2024-03-21 found new gps chip and getting close t oend of schematic
2024-03-23 first pass at routing
2024-03-25 sade
2024-03-25 reciver and stuff
2024-03-26 added batt protection for lyra, added more parts for reciver
2024-03-27 reciver work and finalized lyrav3r1
2024-03-28 work, lyra mostly final
2024-03-28 reciver rework
2024-04-02 post order omcmit
2024-04-03 post sending to watuh
2024-04-06 stuffes
2024-04-09 prod files
2024-04-11 sort of working
2024-04-11 got it mostly working
2024-04-12 fhjyk
2024-04-12 radio working
2024-04-13 reciver kinda working
2024-04-13 bruh
2024-04-13 flight computer mostly working, reciver lcd turning on and radio init
2024-04-13 post flight
2024-04-17 stuff
2024-04-17 maybe hitl?
2024-04-19 stuff
    st
2024-04-23 new hitl test
2024-04-23 cleaning up some stuff
2024-04-23 pre totally converting to library kalman
2024-04-24 kf init
2024-04-24 kf init, orientation broken
2024-04-24 kf kinda working, orientation no longer super bugged
2024-04-25 gps not working but kalman kinda working
2024-04-26 gps might be working?
2024-04-26 gps not working ):
2024-04-27 KF BE BEHAVIN!
2024-04-28 telem working, gps not so much
2024-04-29 radio fixed
2024-05-04 fix cont sensing?
2024-05-06 commets
2024-05-11 log upload
2024-05-12 got real data off, also fixed data printing
2024-05-24 rftyu
2024-05-26 lyrav3r2 init
2024-05-27 woprk
2024-05-31 trying again to get lcd to work, didnt
2024-06-18 work, inital layout
2024-06-21 wokrs
2024-06-24 EOD 6/24
2024-06-25 fixed the crystal cap
2024-06-25 uypadeta
2024-06-25 fabbed
2024-07-03 new boards sort of brought up, gps getting time fix but no pos fix
2024-07-04 updated contiunity checking to work with new boards
2024-07-05 fixed accel axies
2024-07-05 start of drive to far
2024-10-01 shtuff, leo init
2024-10-01 leo workl
2024-10-21 step file
2024-10-28 some bringup
2024-10-30 logging at 50 hz(:
2024-12-15 updates, turns on camera on chan1
2024-12-31 hopefully fix leo printing data
2025-01-03 tried some stuff, didnt work
    remote launch system (sucked)
2025-01-08 launc control attempts
2025-01-23 hope start
2025-01-25 pingpong
2025-01-25 ping pong routing
2025-01-26 ping pong sent for fab
2025-01-27 trilateration???
2025-02-06 hangoverflight pulled
2025-02-06 oh boy
2025-02-08 workin on laerning c!!!!!
2025-02-11 hope initng
2025-02-19 depression
2025-03-20 trying to get cmake to work more
2025-03-21 wtf its like working
2025-03-21 its sorking on laptop nwo
2025-03-24 trying to make it work
2025-03-25 they init now but dont communicate
2025-04-01 small work
2025-05-06 sync
2025-05-08 datacontroller
2025-05-10 it doesnt work - tryied to write custom library
2025-05-11 its communicating w/ sx1280 over spi library
2025-05-11 got packets working back and forth
2025-05-12 start on ranging
2025-05-13 working on adding ranging
2025-05-14 switched to other library which seems to work, trying to get ranging working again
2025-05-21 working kinda
2025-05-24 gps giving trash data
2025-05-28 fixed the gps
2025-07-02 bad commit
2025-07-02 modified: Hope/Firmware/HopeArduino/lib/basiclib/basiclib.h modified: Hope/Firmware/HopeArduino/lib/sx1280lib/src/sx1280lib.cpp modified: Hope/Firmware/HopeArduino/platformio.ini modified: Hope/Firmw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
2025-08-10 it sure is getting hot in here
2025-08-23 it sure is getting hot in here software
2025-08-23 why the fuck does logging data murder the navigation core
2025-08-23 temp logger code working afaik
2025-08-24 data transfer and ranging working in parallel
2025-08-25 yo it could work rn
2025-09-02 tested it and it sucked a lot, maybe i just have to elevate it
    but it is working
2025-09-30 metrumizing it
2025-10-02 new pyro, looking at new RF. still no baord
2025-10-08 dan f10, n511 module, board layout
2025-10-17 saves
2025-10-21 weorjk
2025-12-03 cam control
2025-12-03 first routing pass
2025-12-03 cam control work and start on gruond station
2025-12-04 cam control rework
2025-12-08 camcontrol stm32
2025-12-08 final version?
2025-12-09 rf rework and redrawing
2025-12-09 shit make it good
2025-12-09 please
2025-12-09 fixed dumb issue
2025-12-10 hopefully prod version
2025-12-10 nvm i missed it up
2025-12-16 trying to get hope code working again
2025-12-26 vibecoding ): but app now gets data from serial and logs it to a file
2025-12-26 reconfigure trilateration to happen on ground station
2025-12-27 more work, made ground stations talk to each other
2026-02-03 locks
2026-02-20 duplex coms on stm32hal
2026-02-21 MVP for cam control
2026-03-04 camcontrolfirmware
2026-03-04 tyuil
2026-04-21 ohno
2026-05-24 fixed logging, pre mass storage
2026-05-24 mass storage outputs
2026-05-30 mass storage and junk
